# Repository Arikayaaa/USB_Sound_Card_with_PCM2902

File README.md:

# USB_Sound_Card_with_PCM2902
USB Sound Card with PCM2902, for Headphone and Microphone, High Quality (No Code)

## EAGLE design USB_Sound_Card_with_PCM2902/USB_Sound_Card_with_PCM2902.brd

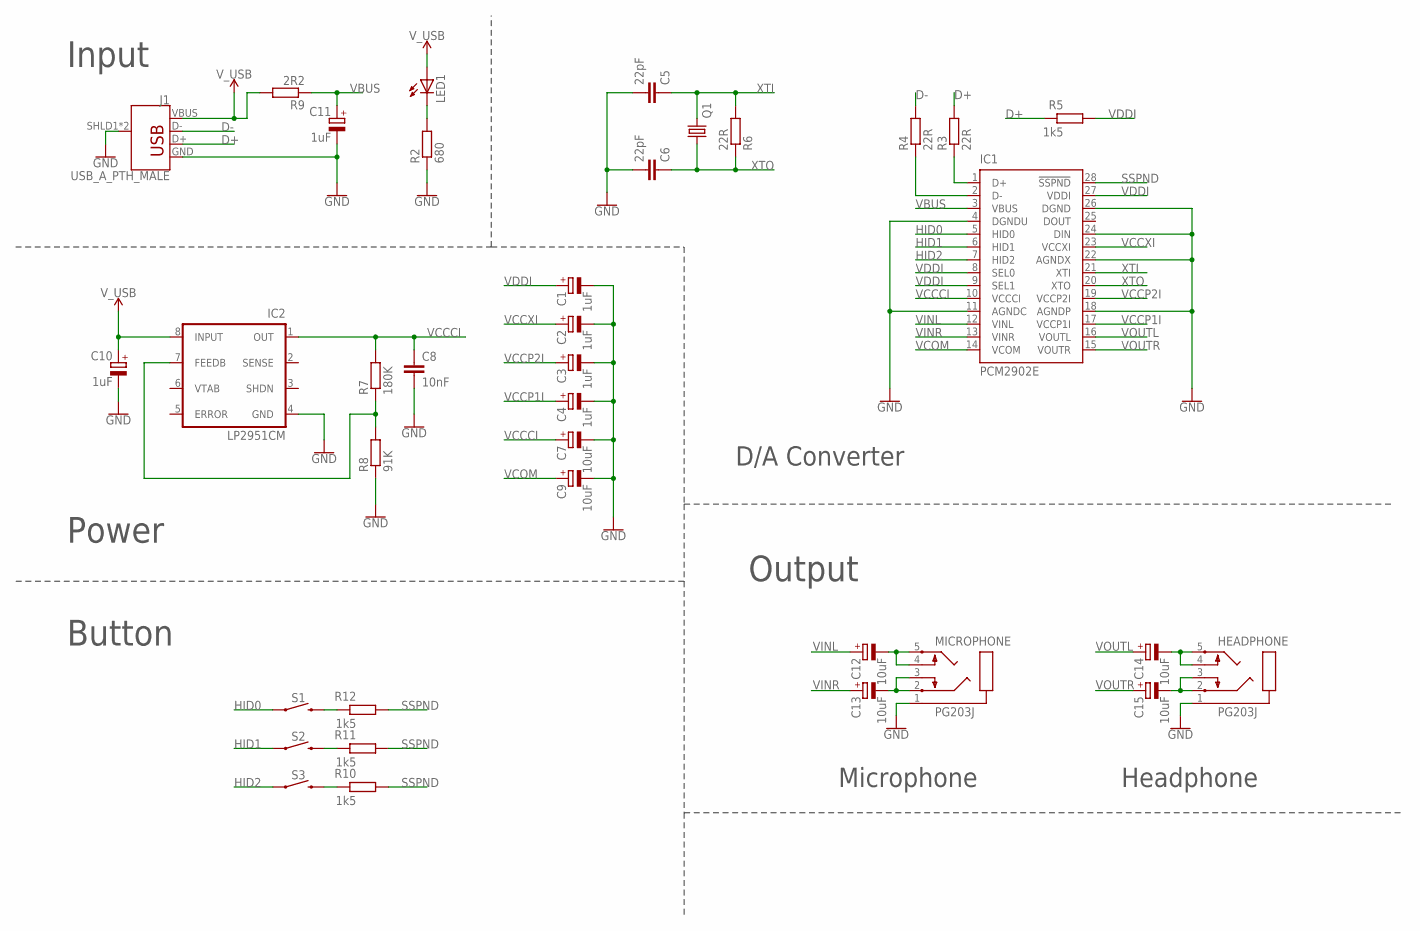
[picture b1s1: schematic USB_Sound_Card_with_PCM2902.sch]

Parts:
C1, C2, C3, C4, C10, C11: 1uF; CT3528
C5, C6: 22pF; C0805
C7, C9, C12, C13, C14, C15: 10uF; CT3528
C8: 10nF; C0805
HEADPHONE: PG203J
IC1: PCM2902E; SSOP28DB
IC2: LP2951CM; SO-08
J1: USB_A_PTH_MALE; USB-A-H
LED1: LEDCHIP-LED0805; CHIP-LED0805
MICROPHONE: PG203J
Q1: CRYSTALHC49UP; HC49UP
R2: 680; M0805
R3, R4, R6: 22R; M0805
R5, R10, R11, R12: 1k5; M0805
R7: 180K; M0805
R8: 91K; M0805
R9: 2R2; M0805
S1, S2, S3: MOMENTARY-SWITCH-SPST-PTH-6.0MM; TACTILE_SWITCH_PTH_6.0MM

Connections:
D+: J1.D+, R3.2, R5.2
D-: J1.D-, R4.2
GND: C1.-, C2.-, C3.-, C4.-, C5.2, C6.2, C7.-, C8.2, C9.-, C10.-, C11.-, HEADPHONE.1, IC1.4 (DGNDU), IC1.11 (AGNDC), IC1.18 (AGNDP), IC1.22 (AGNDX), IC1.24 (DIN), IC1.26 (DGND), IC2.4 (GND), J1.GND, J1.SHLD1 (SHIELD), J1.SHLD2 (SHIELD), MICROPHONE.1, R2.1, R8.1
HID0: IC1.5 (HID0), S1.1
HID1: IC1.6 (HID1), S2.1
HID2: IC1.7 (HID2), S3.1
unnamed: R10.2, S3.3 (2)
unnamed: IC2.7 (FEEDB), R7.1, R8.2
unnamed: R11.2, S2.3 (2)
unnamed: R12.2, S1.3 (2)
unnamed: LED1.C, R2.2
unnamed: IC1.1 (D+), R3.1
unnamed: IC1.2 (D-), R4.1
unnamed: C13.-, MICROPHONE.2, MICROPHONE.3
unnamed: C12.-, MICROPHONE.4, MICROPHONE.5
unnamed: C14.-, HEADPHONE.4, HEADPHONE.5
unnamed: C15.-, HEADPHONE.2, HEADPHONE.3
SSPND: IC1.28 (!SSPND), R10.1, R11.1, R12.1
VBUS: C11.+, IC1.3 (VBUS), R9.1
VCCCI: C7.+, C8.1, IC1.10 (VCCCI), IC2.1 (OUT), R7.2
VCCP1I: C4.+, IC1.17 (VCCP1I)
VCCP2I: C3.+, IC1.19 (VCCP2I)
VCCXI: C2.+, IC1.23 (VCCXI)
VCOM: C9.+, IC1.14 (VCOM)
VDDI: C1.+, IC1.8 (SEL0), IC1.9 (SEL1), IC1.27 (VDDI), R5.1
VINL: C12.+, IC1.12 (VINL)
VINR: C13.+, IC1.13 (VINR)
VOUTL: C14.+, IC1.16 (VOUTL)
VOUTR: C15.+, IC1.15 (VOUTR)
V_USB: C10.+, IC2.8 (INPUT), J1.VBUS, LED1.A, R9.2
XTI: C5.1, IC1.21 (XTI), Q1.2, R6.2
XTO: C6.1, IC1.20 (XTO), Q1.1, R6.1

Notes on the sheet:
Input
Power
Button
Output
Microphone
Headphone
D/A Converter

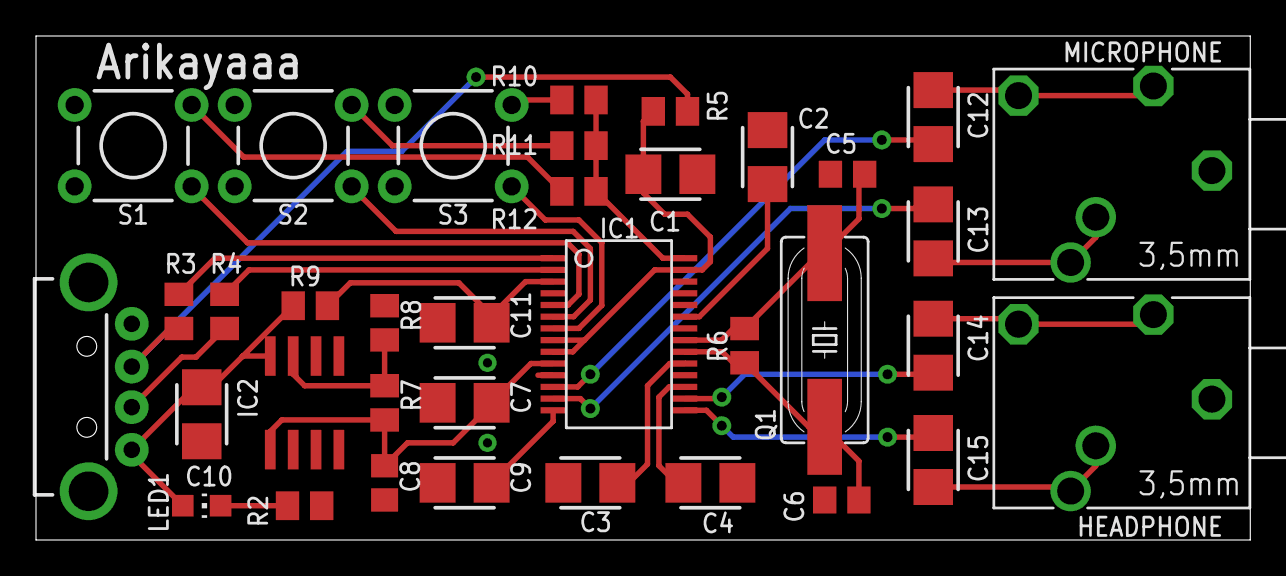
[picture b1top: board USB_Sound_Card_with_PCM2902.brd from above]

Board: 2 copper layers, 67.5 x 28.0 mm, 36 parts (0 on the bottom side), 32 nets.

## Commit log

2020-05-31 v1.00
2022-05-19 v1.01
    Unnecessary recovery files were deleted.
    Gerber files were added

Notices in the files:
parts and their libraries:
SparkFun-Connectors: Licensing: Creative Commons ShareAlike 4.0 International - https://creativecommons.org/licenses/by-sa/4.0
